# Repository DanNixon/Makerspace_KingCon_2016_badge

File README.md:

# KingCon 2016 badge workshop

CAD files for the badge kits for KingCon 2016.

## Parts

- Battery holder: Keystone 3003 ([Mouser](http://www.mouser.co.uk/search/ProductDetail.aspx?R=3003))
- Battery: CR2032 ([Digi-Key](http://www.digikey.co.uk/product-detail/en/panasonic-bsg/CR2032/P189-ND/31939))
- Switch: C&K JS202011CQN ([Mouser](http://www.mouser.co.uk/Search/ProductDetail.aspx?R=JS202011CQN))
- 5mm LEDs

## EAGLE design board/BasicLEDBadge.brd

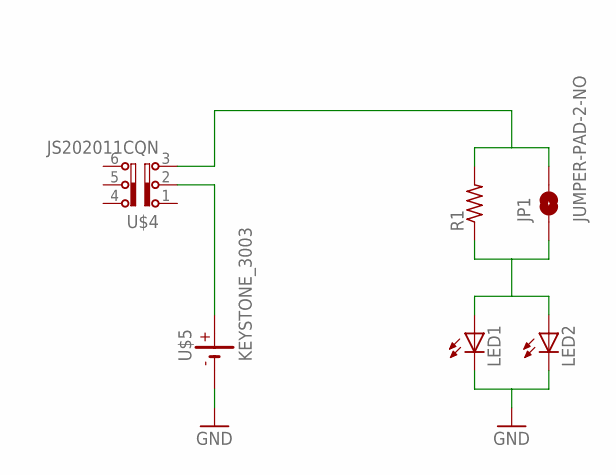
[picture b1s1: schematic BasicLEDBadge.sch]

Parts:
JP1: JUMPER-PAD-2-NO; PAD-JUMPER-2-NO_NO_SILK
LED1, LED2: LED5MM
R1: R-US_0207/9; 0207/9
U$4: JS202011CQN
U$5: KEYSTONE_3003

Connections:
GND: LED1.K (C), LED2.K (C), U$5.P$3 (-)
SW_BATT: JP1.2, R1.2, U$4.3
VBATT: U$4.2, U$5.P$1 (+), U$5.P$2 (+)
VLED: JP1.1, LED1.A, LED2.A, R1.1

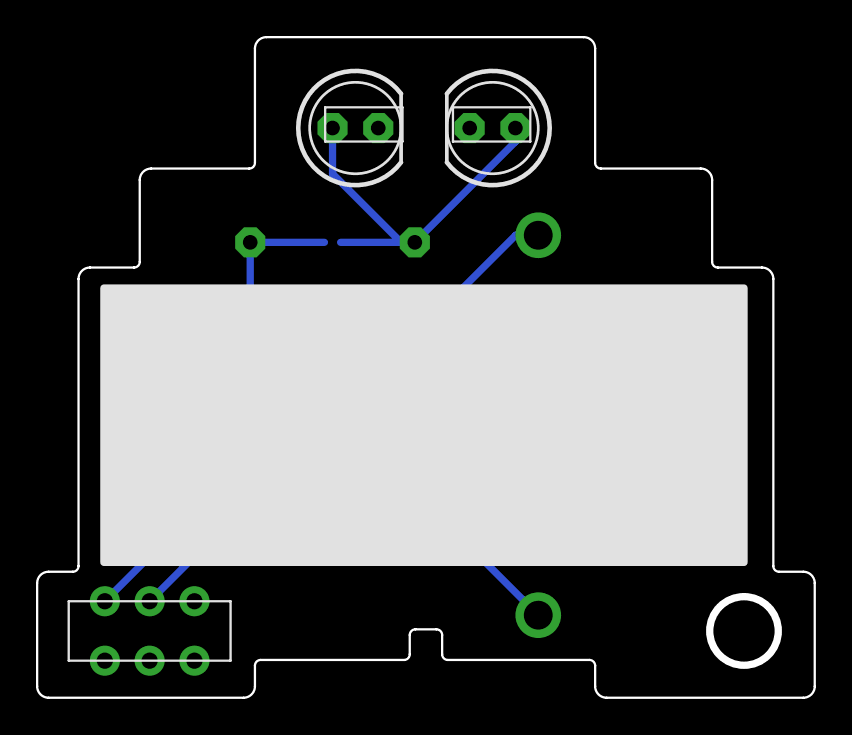
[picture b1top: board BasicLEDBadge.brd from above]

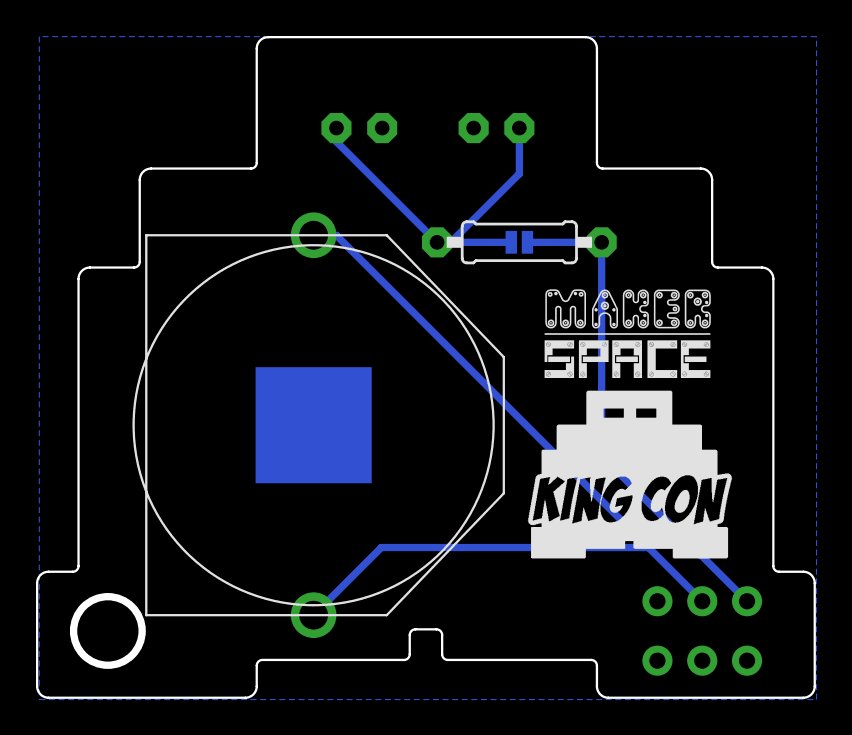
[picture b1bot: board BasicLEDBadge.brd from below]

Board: 2 copper layers, 42.9 x 36.4 mm, 9 parts (5 on the bottom side), 4 nets.

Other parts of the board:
U$1: KINGCON_OUTLINE_48MM
U$2: KINGCON_LOGO_M
U$3: MAKERSPACE_LOGO_FULL_S

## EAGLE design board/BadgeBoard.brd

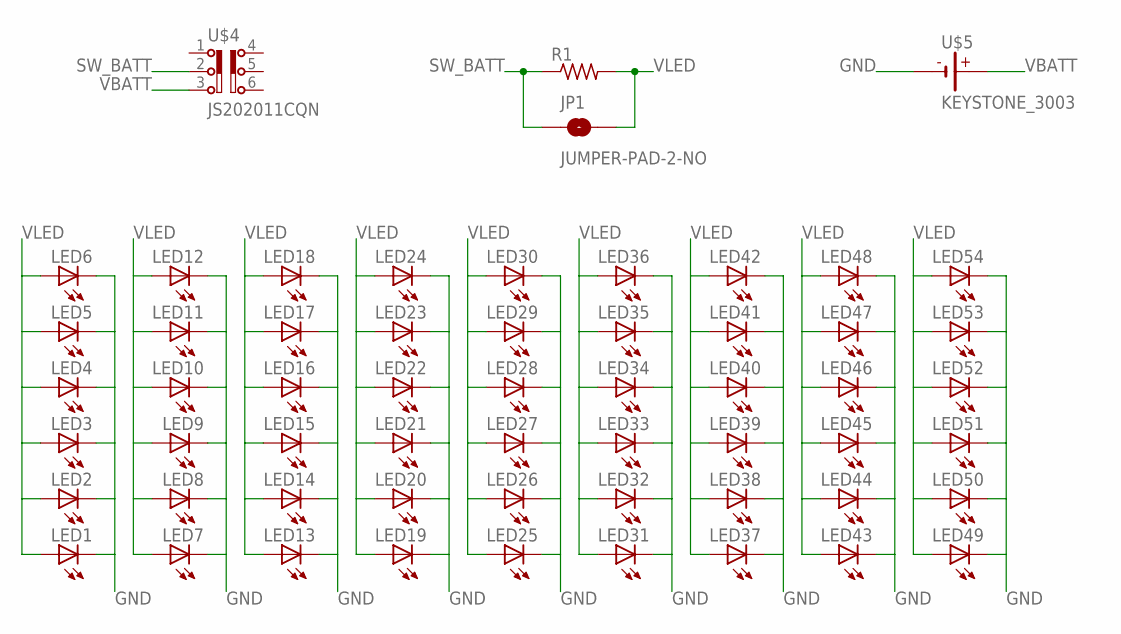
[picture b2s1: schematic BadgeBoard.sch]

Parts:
JP1: JUMPER-PAD-2-NO; PAD-JUMPER-2-NO_NO_SILK
LED1, LED2, LED3, LED4, LED5, LED6, LED7, LED8, LED9, LED10, LED11, LED12, LED13, LED14, LED15, LED16, LED17, LED18, LED19, LED20, LED21, LED22, LED23, LED24, LED25, LED26, LED27, LED28, LED29, LED30, LED31, LED32, LED33, LED34, LED35, LED36, LED37, LED38, LED39, LED40, LED41, LED42, LED43, LED44, LED45, LED46, LED47, LED48, LED49, LED50, LED51, LED52, LED53, LED54: LED3MM
R1: R-US_0207/9; 0207/9
U$4: JS202011CQN
U$5: KEYSTONE_3003

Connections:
GND: LED1.K (C), LED2.K (C), LED3.K (C), LED4.K (C), LED5.K (C), LED6.K (C), LED7.K (C), LED8.K (C), LED9.K (C), LED10.K (C), LED11.K (C), LED12.K (C), LED13.K (C), LED14.K (C), LED15.K (C), LED16.K (C), LED17.K (C), LED18.K (C), LED19.K (C), LED20.K (C), LED21.K (C), LED22.K (C), LED23.K (C), LED24.K (C), LED25.K (C), LED26.K (C), LED27.K (C), LED28.K (C), LED29.K (C), LED30.K (C), LED31.K (C), LED32.K (C), LED33.K (C), LED34.K (C), LED35.K (C), LED36.K (C), LED37.K (C), LED38.K (C), LED39.K (C), LED40.K (C), LED41.K (C), LED42.K (C), LED43.K (C), LED44.K (C), LED45.K (C), LED46.K (C), LED47.K (C), LED48.K (C), LED49.K (C), LED50.K (C), LED51.K (C), LED52.K (C), LED53.K (C), LED54.K (C), U$5.P$3 (-)
SW_BATT: JP1.1, R1.1, U$4.2
VBATT: U$4.3, U$5.P$1 (+), U$5.P$2 (+)
VLED: JP1.2, LED1.A, LED2.A, LED3.A, LED4.A, LED5.A, LED6.A, LED7.A, LED8.A, LED9.A, LED10.A, LED11.A, LED12.A, LED13.A, LED14.A, LED15.A, LED16.A, LED17.A, LED18.A, LED19.A, LED20.A, LED21.A, LED22.A, LED23.A, LED24.A, LED25.A, LED26.A, LED27.A, LED28.A, LED29.A, LED30.A, LED31.A, LED32.A, LED33.A, LED34.A, LED35.A, LED36.A, LED37.A, LED38.A, LED39.A, LED40.A, LED41.A, LED42.A, LED43.A, LED44.A, LED45.A, LED46.A, LED47.A, LED48.A, LED49.A, LED50.A, LED51.A, LED52.A, LED53.A, LED54.A, R1.2

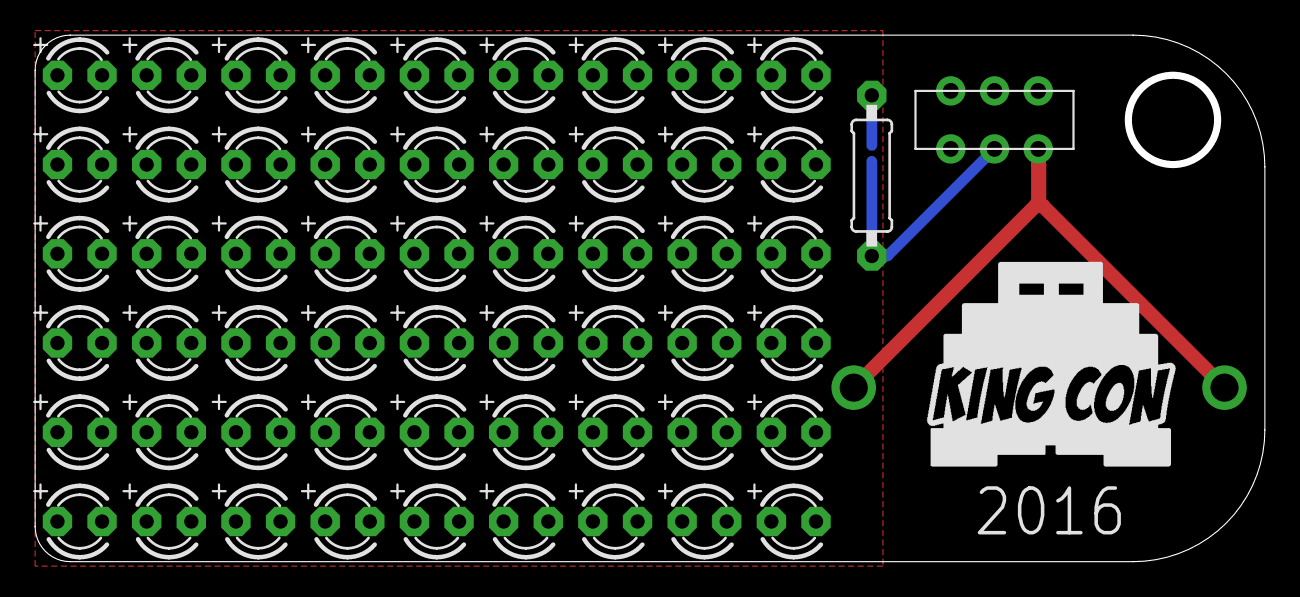
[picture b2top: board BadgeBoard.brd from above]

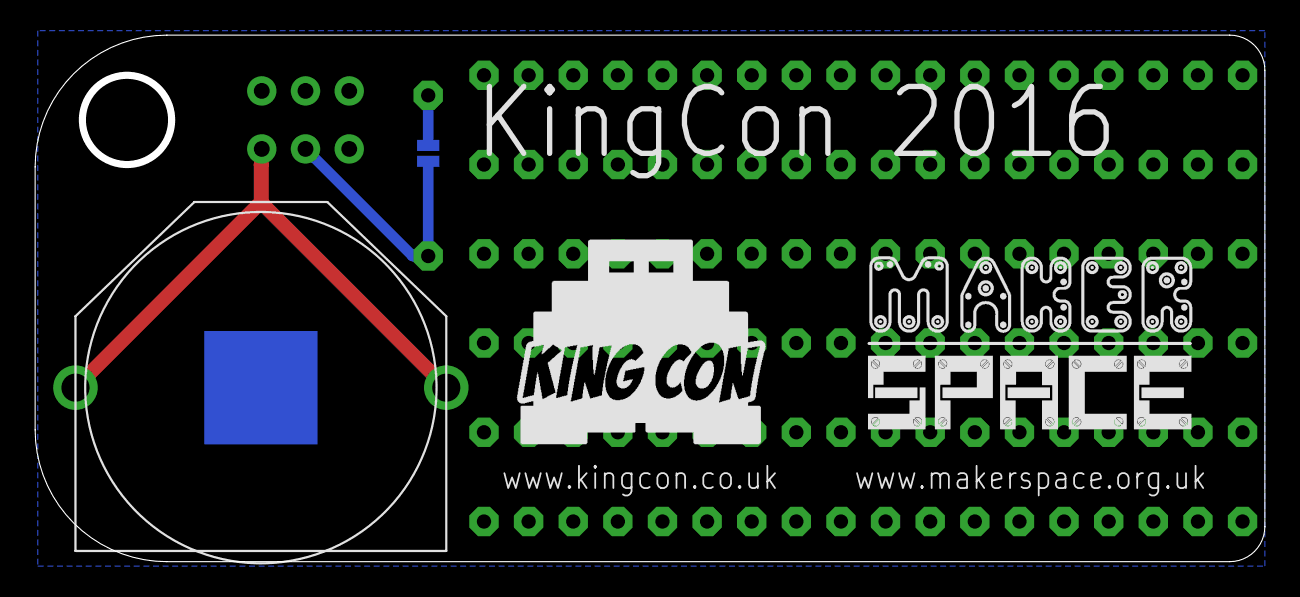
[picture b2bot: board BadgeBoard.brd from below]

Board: 2 copper layers, 69.6 x 29.6 mm, 61 parts (4 on the bottom side), 4 nets.

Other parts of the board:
U$1, U$3: KINGCON_LOGO_L
U$2: MAKERSPACE_LOGO_FULL_M

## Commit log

2016-07-13 initial test board
2016-07-14 update led matrix
2016-07-21 More layout
2016-07-31 Add logos
2016-08-12 list parts
2016-08-12 add switch and i-lim res
2016-08-12 move to dir
2016-08-12 add battery, redo layout a little
2016-08-13 readd battery clip
2016-09-24 add basic board
2016-09-27 new board design
2016-09-28 fix small issues

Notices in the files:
parts and their libraries:
SparkFun-Passives: Licensing: Creative Commons ShareAlike 4.0 International - https://creativecommons.org/licenses/by-sa/4.0
